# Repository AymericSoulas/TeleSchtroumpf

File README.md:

# TeleSchtroumph
A short projet for animating children activities around the smurf's universe. A device with a mushroom shape which you can send phrases to. It will the translate them in morse code and flash them on a light.

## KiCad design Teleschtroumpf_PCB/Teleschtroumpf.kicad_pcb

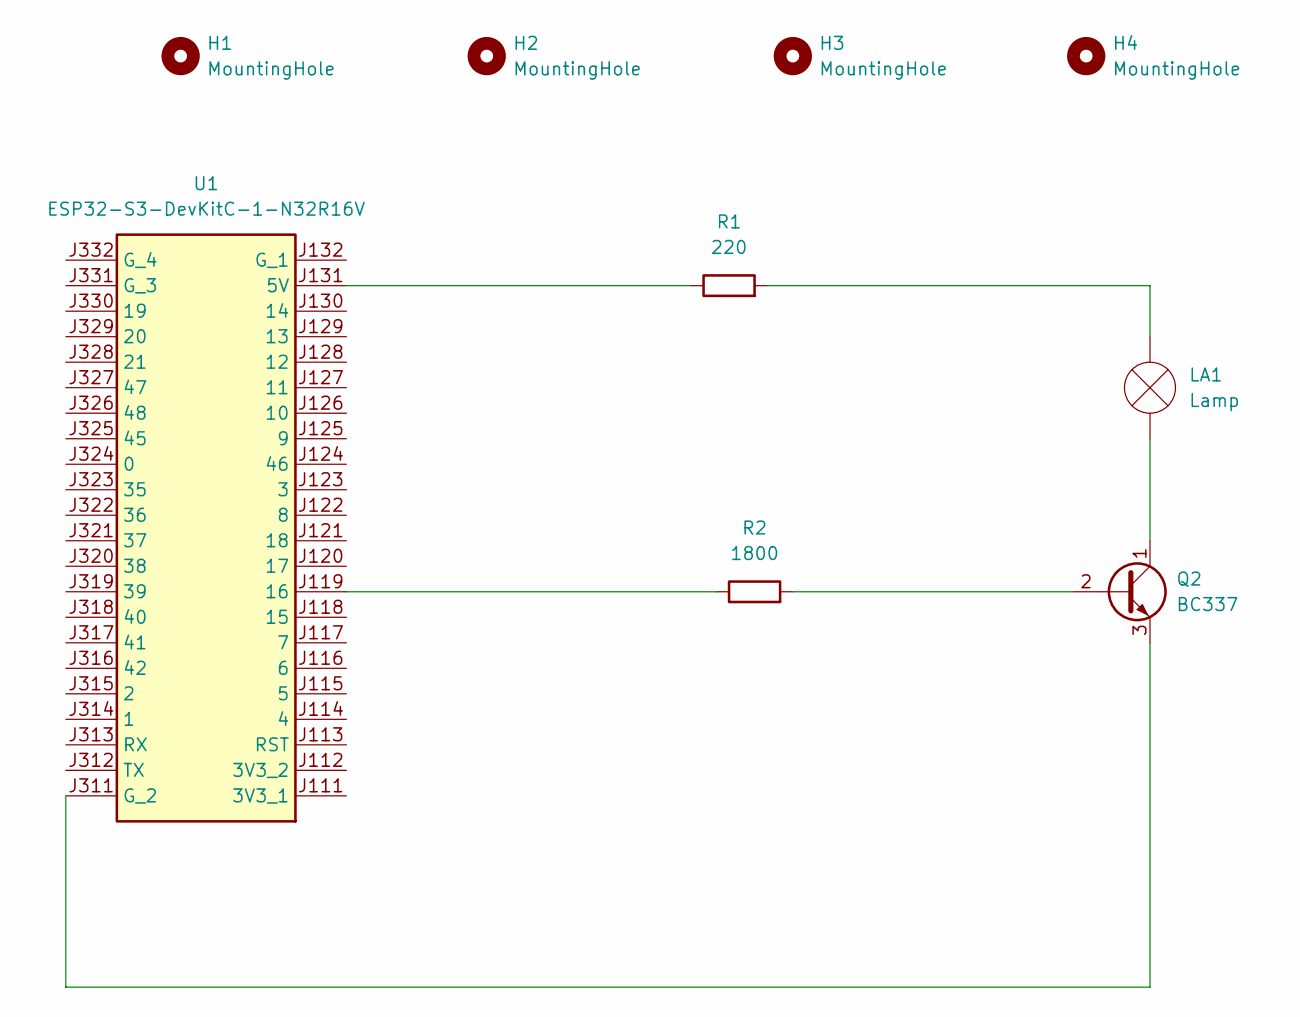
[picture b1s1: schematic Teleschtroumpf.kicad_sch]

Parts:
H1, H2, H3, H4: MountingHole; MountingHole_2.1mm
LA1: Lamp; R_Axial_DIN0207_L6.3mm_D2.5mm_P15.24mm_Horizontal
Q2: BC337; TO-92_Inline
R1: 220; R_Axial_DIN0207_L6.3mm_D2.5mm_P15.24mm_Horizontal
R2: 1800; R_Axial_DIN0207_L6.3mm_D2.5mm_P15.24mm_Horizontal
U1: ESP32-S3-DevKitC-1-N32R16V; ESP32S3DevKitC1N32R16V; Manufacturer_Part_Number ESP32-S3-DevKitC-1-N32R16V; Mouser Part Number 356-32S3DKTC1N32R16V

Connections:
unnamed: LA1.2 (+), R1.2
unnamed: LA1.1 (-), Q2.1 (C)
unnamed: Q2.2 (B), R2.2
unnamed: Q2.3 (E), U1.J311 (G_2)
unnamed: R1.1, U1.J131 (5V)
unnamed: R2.1, U1.J119 (16)

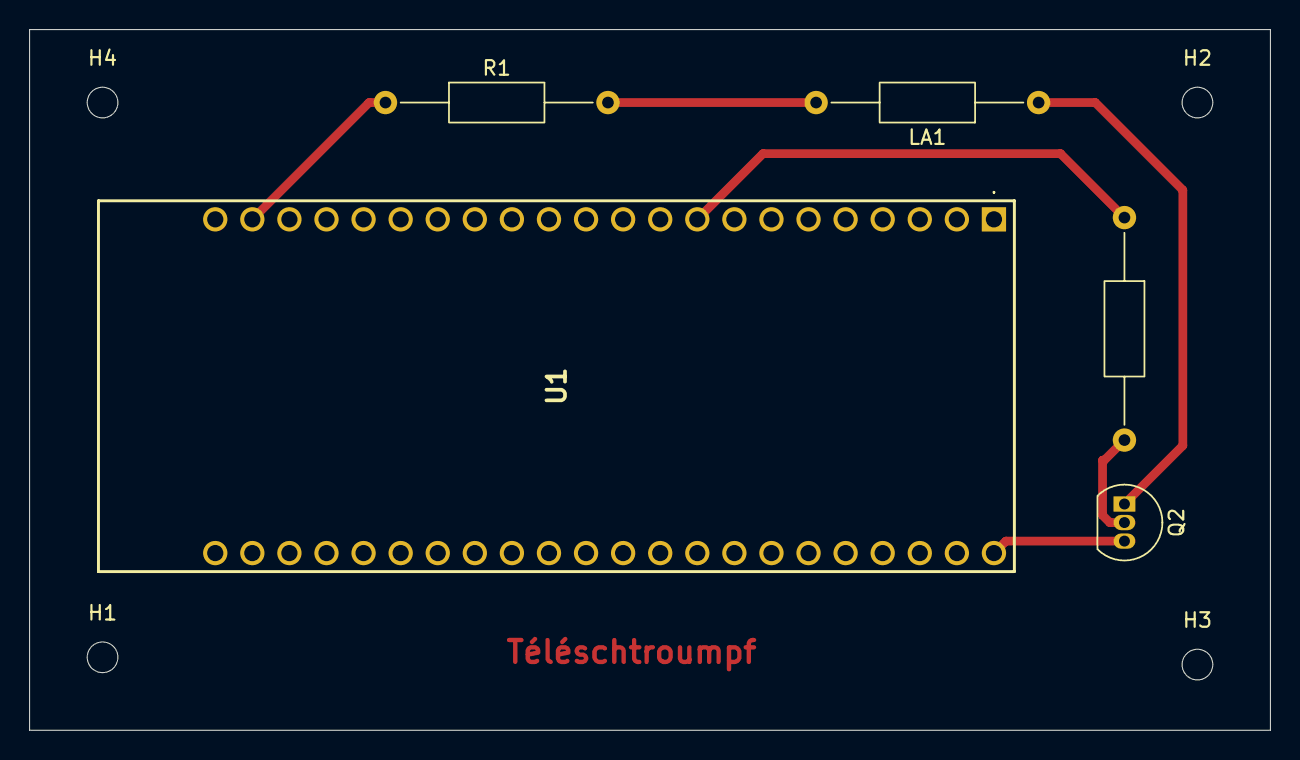
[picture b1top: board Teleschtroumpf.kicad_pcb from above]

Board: 2 copper layers, 85.0 x 48.0 mm, 9 parts (0 on the bottom side), 6 nets.

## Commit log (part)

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2026-06-23 Migration local ==> Github
2026-06-23 Typing Error corrected
2026-06-24 WiFi-Server + Morse translate
2026-06-24 Delete Teleschtroumph_Code directory
    This folder was renamed Teleschtroumpf to comply with Arduino IDE
2026-06-24 Delete Teleschtroumph_PCB directory
    This directory was renamed because of a mistake at creation.
